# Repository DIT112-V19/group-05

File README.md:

# Route Design - The HAJKEN Car

<html> </html>

## What?

<i>“You draw, it drives!”</i>

An Android App in which the user can draw a (free-hand) route. The vehicle will drive according to the drawn route and, if requested, reverse and repeat it. Additionally, the vehicle can get its current GPS location and drive according to a track based on a route planned in google maps.

## Why?
The interface enables a simple way of controlling the vehicle without programming. Driving according to certain user-drawn route and reversing/repeating this route, can be used for:
* data collection 
* surveillance of area

There are many more applicable areas where there is use of a designed and predetermined route.

## How?
### Software:
#### for App
* Android Studio

#### for Arduino
* Arduino IDE
* Arduino libraries:
  * <a href="https://github.com/platisd/smartcar_shield">smartcar shield</a> by Dimitris Platis (*)
  * <a href="https://playground.arduino.cc/Code/NewPing/">NewPing</a> by Tim Eckel (*)
  * <a href="http://arduiniana.org/libraries/tinygpsplus/">TinyGPS++</a> by Mikal Hart
  
  (*) available via Arduino IDE  

### Hardware:
* Mobile Phone with Android OS and Bluetooth
* Arduino Mega
*  <a href="https://github.com/platisd/smartcar_shield/tree/master/extras/eagle/smartcar_shield">PCB Smartcar Shield</a>
* 4x DC motors
* Bluetooth module
* Sensors:
	* 2x UltraSonicSound Sensor (HC-SR04)
	* Odometer (speed encoders)
	* Gyroscope
	* GPS-module (Neo-6M)
* BETA: Hajken PCB with 3 LEDs and connections for sensors (see: pcb/hajken_cutouts_v2/)

## Setup and get Started

### Download repository
https://github.com/DIT112-V19/group-05/archieve/master.zip

### Car / Hardware
1. Follow the <a href="https://www.hackster.io/platisd/getting-started-with-the-smartcar-platform-1648ad">instructions</a> for the hardware setup of the smartcar with differential control (aka driving like a tank) 
2. Connect front UltraSonic Sensor to pin 51 (trigger) & pin 52 (echo) [or other equivalent free pins]
3. Connect right-side UltraSonic Sensor to pin 5 (trigger) & pin 6 (echo) [or other equivalent free pins] (or plugin into pins marked "Sensor right" on *Hajken PCB*)
4. Connect odometer to pin 3 (additional odometer: connect to pin 2) (or plugin into pins marked "Odometer right"/"Odometer left" on *Hajken PCB*)
5. Connect Bluetooth module to (hardware) serial 3 (pin 15(RX) & 14(TX) - connect RX to TX, TX to RX)
6. Connect GPS module to (hardware) serial 1 (pin 19(RX) & 18(TX) - connect RX to TX, TX to RX)

Hardware setup (with *Hajken PCB*):
<html>   </html>

### Arduino
1. Open hajkenCar.ino in Arduino IDE
2. Download the above-mentioned libraries (via Arduino IDE) and install TinyGPS++ manually (library folder must be called "TinyGPS++")
3. Adjust pin setup if necessary. 
4. Calibrate odometer(s) and gyroscope. Use Smartcar Shield sketches for calibration (Odometer: sensors->odometer->FindPulsesPerMeter / Gyroscope: sensors->odometer->GyroscopeCalibration). Update PULSES_PER_METER and GYRO_OFFSET values.
5. Optional: Test Sensors. Smartcar Shield library includes several sketches to test sensors' functionality.
6. Upload sketch to your Arduino Smartcar.

### Android Application

**1. Import Android Project**
* Open Android Studios
* Choose import project
* Select android inside of the cloned folder
* Follow setup instructions

**2. Create an API-key for Google Directions API** <br />
*This is required for the application to build.*<br />
* Go to the <a href="https://cloud.google.com/console/google/maps-apis/overview">Google Cloud Platform Console</a> .
* From the Project drop-down menu, select or create the project for which you want to add an API key.
* From the  Navigation menu, select APIs & Services > Credentials.
* On the Credentials page, click Create credentials > API key. <br />
The API key created dialog displays your newly created API key.
* Open the Android folder
* Create a copy of the file gradle.properties.no.git and name it gradle.properties
* Open gradle.properties
* Find line 15 where it says GoolgeAPIKey = "myKey"
* Insert your API-key where it says "myKey"

**3. Build and run the app in Android Studios** <br />
Tutorial for detailed instructions: https://developer.android.com/studio/run

**4. Give app permission to use location** <br />
Once the application is running, it needs permission to use the phones location.

| <html>   </html> |   <html>   </html> |   <html>   </html> |
 | --- | --- | --- |
| a). Open Settings. Go to Permissions | b). Go to Your Location | c). Enable permission for the app |

**5. The application is ready for using**

## Navigate through the interface

The basic navigation through the app can be seen in the following 3 pictures:

| Connect to car | Draw and drive | Map and drive |
  | --- | --- | --- |
| <html>   </html> |  <html>   </html> |   <html>   </html> |

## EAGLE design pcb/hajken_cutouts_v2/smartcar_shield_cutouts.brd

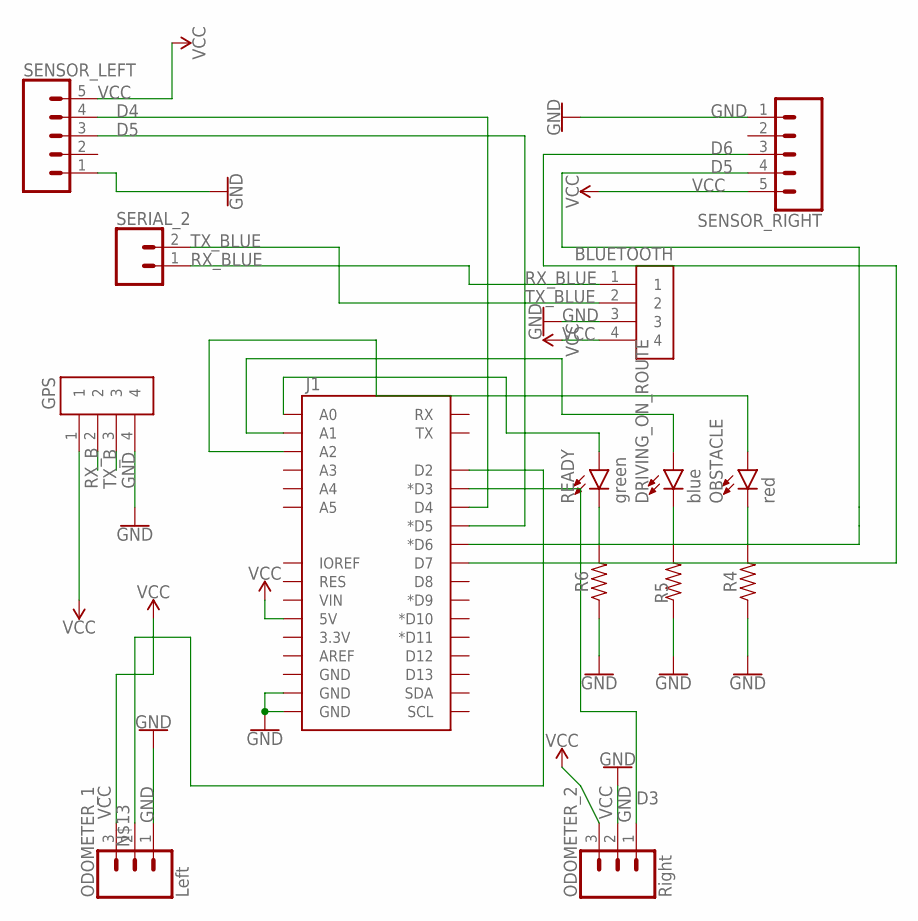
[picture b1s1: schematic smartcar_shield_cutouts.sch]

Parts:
BLUETOOTH: 1X4-BIG; 1X04-BIG
DRIVING_ON_ROUTE: blue; LED_5MM
GPS: 1X4-BIG; 1X04-BIG
J1: ARDUINO_R3_SHIELDUNO_R3_SHIELD_LOCK; UNO_R3_SHIELD_LOCK
OBSTACLE: red; LED_5MM
ODOMETER_1: Left; 1X03
ODOMETER_2: Right; 1X03
R4, R5, R6: AXIAL-0.3
READY: green; LED_5MM
SENSOR_LEFT: CONN_05; 1X05
SENSOR_RIGHT: CONN_05; 1X05
SERIAL_2: CONN_02; 1X02

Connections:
D3: J1.D3 (*D3), ODOMETER_2.1
D4: J1.D4, SENSOR_LEFT.4
D5: J1.D5 (*D5), J1.D6 (*D6), SENSOR_LEFT.3, SENSOR_RIGHT.4
D6: J1.D7, SENSOR_RIGHT.3
GND: BLUETOOTH.3, GPS.4, J1.GND@0 (GND), J1.GND@1 (GND), ODOMETER_1.1, ODOMETER_2.2, R4.P$1 (1), R5.P$1 (1), R6.P$1 (1), SENSOR_LEFT.1, SENSOR_RIGHT.1
unnamed: R6.P$2 (2), READY.K (C)
unnamed: DRIVING_ON_ROUTE.K (C), R5.P$2 (2)
unnamed: OBSTACLE.K (C), R4.P$2 (2)
unnamed: DRIVING_ON_ROUTE.A, J1.A1
unnamed: J1.D2, ODOMETER_1.2
unnamed: J1.A2, OBSTACLE.A
unnamed: J1.A0, READY.A
RX_B: GPS.2
RX_BLUE: BLUETOOTH.1, SERIAL_2.1
TX_B: GPS.3
TX_BLUE: BLUETOOTH.2, SERIAL_2.2
VCC: BLUETOOTH.4, GPS.1, J1.5V, ODOMETER_1.3, ODOMETER_2.3, SENSOR_LEFT.5, SENSOR_RIGHT.5

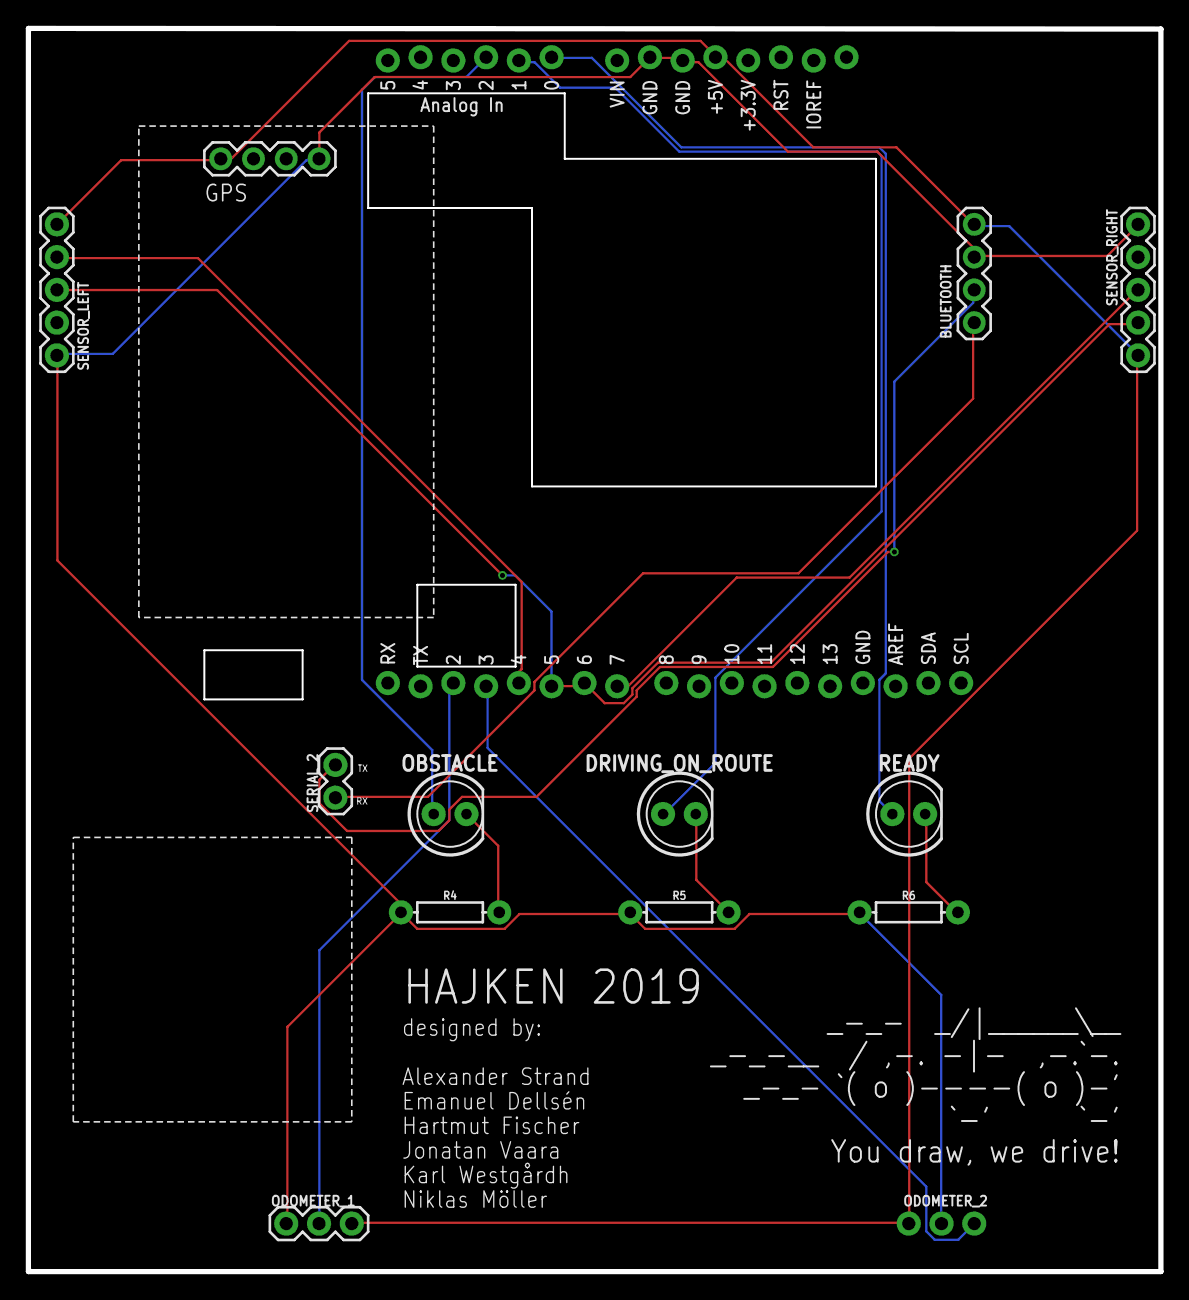
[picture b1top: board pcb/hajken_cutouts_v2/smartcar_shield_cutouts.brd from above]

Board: 2 copper layers, 87.8 x 96.4 mm, 14 parts (1 on the bottom side), 15 nets.

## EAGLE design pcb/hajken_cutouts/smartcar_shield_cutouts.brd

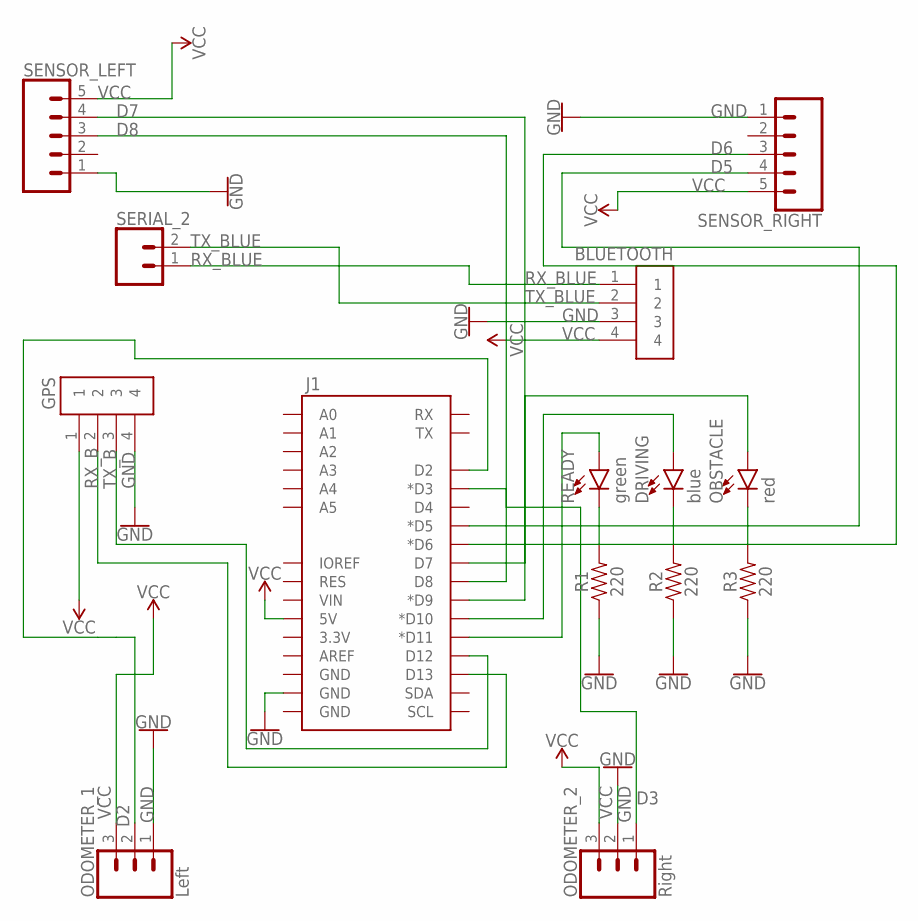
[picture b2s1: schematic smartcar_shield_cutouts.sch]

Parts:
BLUETOOTH: 1X4-BIG; 1X04-BIG
DRIVING: blue; LED_5MM
GPS: 1X4-BIG; 1X04-BIG
J1: ARDUINO_R3_SHIELDUNO_R3_SHIELD_LOCK; UNO_R3_SHIELD_LOCK
OBSTACLE: red; LED_5MM
ODOMETER_1: Left; 1X03
ODOMETER_2: Right; 1X03
R1, R2, R3: 220; 0603
READY: green; LED_5MM
SENSOR_LEFT: CONN_05; 1X05
SENSOR_RIGHT: CONN_05; 1X05
SERIAL_2: CONN_02; 1X02

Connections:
D2: J1.D2, ODOMETER_1.2
D3: J1.D3 (*D3), ODOMETER_2.1
D5: J1.D5 (*D5), SENSOR_RIGHT.4
D6: J1.D6 (*D6), SENSOR_RIGHT.3
D7: J1.D7, SENSOR_LEFT.4
D8: J1.D8, SENSOR_LEFT.3
GND: BLUETOOTH.3, GPS.4, J1.GND@1 (GND), ODOMETER_1.1, ODOMETER_2.2, R1.1, R2.1, R3.1, SENSOR_LEFT.1, SENSOR_RIGHT.1
unnamed: R1.2, READY.K (C)
unnamed 15: DRIVING.K (C), R2.2; also elsewhere on the board
unnamed: OBSTACLE.K (C), R3.2
unnamed: J1.D11 (*D11), READY.A
unnamed 19: DRIVING.A, J1.D10 (*D10); also elsewhere on the board
unnamed: J1.D9 (*D9), OBSTACLE.A
RX_B: GPS.2, J1.D13
RX_BLUE: BLUETOOTH.1, SERIAL_2.1
TX_B: GPS.3, J1.D12
TX_BLUE: BLUETOOTH.2, SERIAL_2.2
VCC: BLUETOOTH.4, GPS.1, J1.5V, ODOMETER_1.3, ODOMETER_2.3, SENSOR_LEFT.5, SENSOR_RIGHT.5

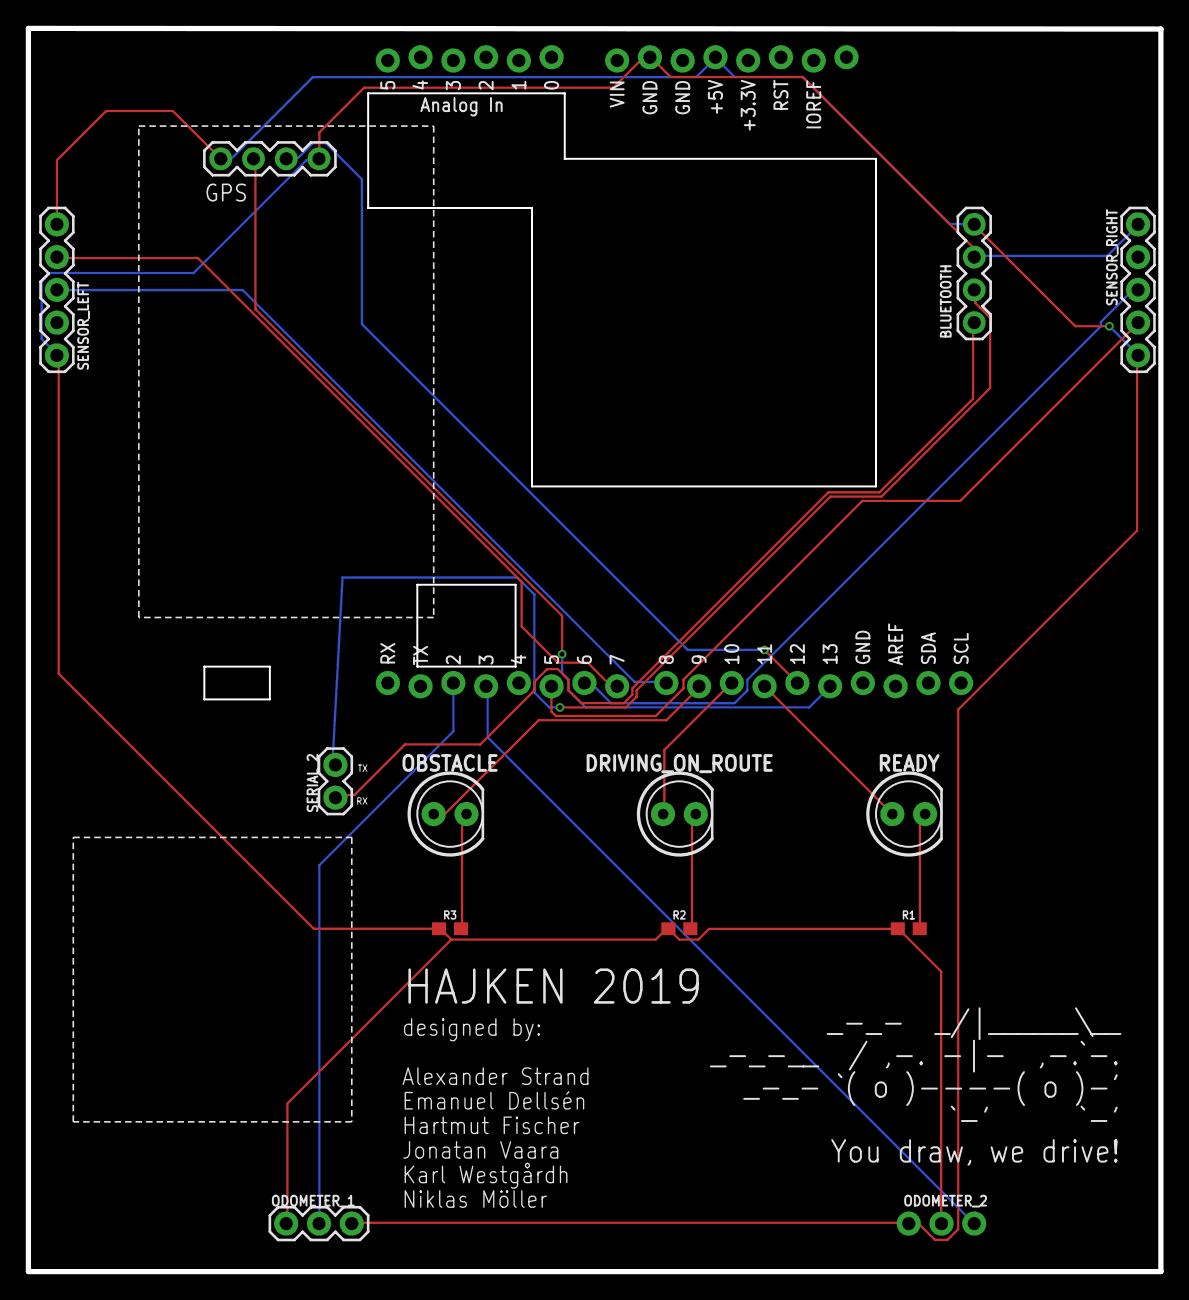
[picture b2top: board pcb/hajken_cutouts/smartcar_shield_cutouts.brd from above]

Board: 2 copper layers, 87.8 x 96.4 mm, 14 parts (1 on the bottom side), 18 nets.

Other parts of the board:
DRIVING_ON_ROUTE: blue; LED_5MM

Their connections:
unnamed 15: DRIVING_ON_ROUTE.K; also elsewhere on the board
unnamed 19: DRIVING_ON_ROUTE.A; also elsewhere on the board

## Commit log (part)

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2019-04-04 Subject:Olivers readme
2019-04-05 Create .gitignore
    Added a gitignore that covers; Intellij, Eclipse, Arduino, Android studios
2019-04-05 Subject: Add README file
    Describe why, how and what
2019-04-08 Added issue template
    Including labels, assignees and acceptance criteria
2019-04-10 Subject: Fixed basic layout
    Changed layout of the different fragments.
    Removed unnescessary green bar from top of the screen.
2019-04-10 Subject: Add basic forward/backward function
    Add forward driving function
    Add backward driving function
2019-04-10 Subject: Choice of route
    ImageButtons for choice of circle route or square route
    Included customDialog to interface
    Included customDialog via interface to mainActivity, used to display
    messages
    Included toast in mainactivity
2019-04-11 Subject: Integration of bluetooth
    Description:
    Starting the integration of bluetooth connectivity with the app.
    Updated class "scanFragment"
2019-04-11 Subject: Integrated bluetooth to code
    Description: Now scan for devices works, it produces a list of devices
    found and you can choose device and establish a bluetooth connection
    between your phone and that device.
2019-04-12 Subject:
2019-04-12 Subject: Fixed Layout
    Improved the layout of the app to look better.
    The buttons are now symmetrical.
    Added border to the device list.
    Added a colour for our standard background, however, standard background
    doesn't work yet.
2019-04-12 Subject: {SUBJECT_TITLE}
    {DESCRIPTION}
    Related Issue(s):
2019-04-14 Subject: Fixed "Stop Vehicle Button" states
    Changed the switch case in CollectionFragment so that the button changes
    states when user clicks on it.
    Now it represents the true state of the button (I Think)
    Fixes #21
2019-04-14 Subject: Add stop vehicle button
    - Stop vehicle button deactivated until vehicle has started
    - Stop vehicle button has its own related dialog
    - Collections and onbackPressed deactivated when vehicle has started
    Related issues:
    - Relates to #21
    - Relates to #20
2019-04-15 Subject: Minor changes regarding bluetooth connectivity
    Description: No big changes done
2019-04-15 Subject: Fix toasts and dialog changes
    Fix toast when onBackPressed
    Fix toast when cancelDialoge
    Change one line background color for pair_button
    Related Issues
    Relates to #21
2019-04-15 Subject: Add canvasDraw
    Add a way to draw on a canvas.
    Make sure it is only possible to make one line at a time.
    Give canvas a frame.
    Related Issues:
    Relates to #27
    Relates to #28
2019-04-16 Subject: Minor changes to bluetooth
    Description: Minor changes to bluetooth class
2019-04-17 Subject: Fix rotate function
    Why: To be able to make the car rotate
    What: Reading gyroscope value, to turn specified amount of angle
    Related Issue(s):
    Relates to #13 , #11
2019-04-17 Subject: Add function to stop vehicle
    Why: To be able to stop the vehicle, while moving
    What: Stop function that reads from serial, looks for 's' to stop
    Related Issue(s):
    Relates to #17 , #20
2019-04-29 Subject: Add vector calculation
    Coordinates saved are now relevant to the direction and rotation of the
    vehicle
2019-04-29 Subject: Correct coordinate conversion
    - Corrected coordinate conversion
    - Able to send instructions to vehicle via bluetooth
2019-04-30 Subject: Clean up and comments
    Why: Making code look good and understandable
    What: Clean up irrelevant code and add some comments
    Authors:
    Related Issue(s): Relates to #31
2019-05-02 Subject: Add RDP-algorithm
    Description: Add RDP-algorithm to simplify polyline drawn from
    application
2019-05-03 Subject: Reverse commands and rounds to drive
    Why: Being able to going back and forth on a predetermined route
    What: Reading command inputs backwards and executing them. Executing
    commands for a given amount of time
    Authors: Co-authored-by: HarFis <gusfisha@student.gu.se>
    Related Issue(s): Fixes #32 , Relates to #39
2019-05-03 Subject: Merge commented and reverse function
2019-05-03 Subject: Fixed instructions rotation
    Description:
    - Fixed coordinateConverter rotation for user interface
    - Changed instructions syntax for reverse/loop
2019-05-03 Subject: Added function to call vechile for GPS-data
    Description: Inserted BluetoothConnection in OnAttach
    Relates #37 & #41
2019-05-03 Subject: Notify when no connection in collection
    Create a toast to display to the user which says "Not Connected to a
    device". This is only for the Collection Fragment.
    This will help the user-experience.
2019-05-06 Subject: Button funcionality and show device
    Add Button functionality in the drawFragment.
    Connected device is now displayed in some of the fragments.
2019-05-06 travis setup
2019-05-06 Subject: Colour changes
    Changed colours for the buttons and the Fragments' background
2019-05-06 Update .travis.yml
    Removed duplicate code which disabled the CI
2019-05-06 Subject: Change position of google maps-fragment entry
    Description:
    - Change position of google maps-fragment entry to gatewayFragment
2019-05-06 Subject: RecyclerView
    Add basic recyclerView functionality.
    It is scorlled verically instead of horizontally for now.
    Also, the pictures have no onClickListeners yet.
    Relates to #52
2019-05-06 Subject: Deleted unused arduino file
    Description: Deleted unused arduino file that is unused and causes error
    upon running travis.yml script
2019-05-06 Update ExampleInstrumentedTest.java
    Change in the androidTest folder because it gave an error in the travis CI test
2019-05-06 Update .travis.yml
    Update to a newer tinyGPSPlus library in the travis.yml
2019-05-07 Update .travis.yml
    Add a way to deal with the library based on a suggestion from @platisd
2019-05-08 Update hajkenCar.ino
    Remove merge conflicts
2019-05-08 Subject: Refractoring
    Removal of unused classes
2019-05-08 Subject: Heading correction and stoping method
    Why: Veichle should drive in a straight line, vechile should be able to
    stop
    What: Method that checks veichle current heading and corrects the
    heading with differnet motor speed, update speed to three different
    choices
    Authors: Co-authored-by: HarFis <gusfisha@student.gu.se>
2019-05-08 Subject: Add working recyclerView
    Add functionallity when pressing images in recyclerView.
    Also, add nested ArrayList with coordinates in OurData.
    Fixes #52
2019-05-08 Subject: Add radiogroup/buttons
    Description:
    - Add radiogroup to drawFragment and collectionFragment
    - Add radiobutton to drawFragment and collectionFragment to change speed
    of vehicle instructions
2019-05-08 Subject: add button states
    Description:
    - Add button correct states
    - Add button layout
2019-05-10 Subject: Fix buttons
    Add buttons to mapFragment.
    Change name of buttons on draw and collection.
2019-05-10 Subject: Add PCB cutout files
2019-05-10 Subject: Add dialog fragment, button states in scan fragment, listener
    Description: Add a dialog fragment in draw fragment from which you can start and stop the car. Altered button states in scan fragment so they adapt with bluetooth status with the use of interface and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
    Fixes #42
    Relates to #51
2019-05-11 Subject: Update PCB board - ready for production
2019-05-12 Subject: Add listener to collection fragment
    Description: In progress to fully add listener to collection fragment to
    control button states and clarify connection status between devices
2019-05-12 Subject: Add bitmaps to recycler view
    Description: Add bitmaps to recycler view, class to bind each bitmap
    together with its respective coordinates
2019-05-13 Subject: Change small fix
    relate(s): #69
2019-05-13 Subject: Set API-key in Travis as enviroment variable
    Description: Set API-key as enviroment variable in the Travis Settings.
2019-05-14 Subject: Add bluetooth not enabled check
    Description:
    - Add bluetooth not enabled / non-existing check
2019-05-14 Subject: Add startPoint and display of actual route
    Description:
    - Add startPoint to canvas onDraw
    - Add display of actual route on canvas
    - Change color of drawn route to differ between drawn route and actual
    route
2019-05-15 Subject: Add dialog window to collection fragment
    Description: Add dialog window to collection fragment so that the user can alter speed of saved routes and number of repetitions then starts car after pressing start in the dialog window
2019-05-15 Subject: Add GPS function
    Why: Get position from GPS modul on start of map modus
    What: Read GPS signal on start of map modus, wait until GPS fix, leave on signal from app
    relates #70
2019-05-15 Subject: Removed one line from String.xml
2019-05-16 Subject: Start refactor bluetooth
    Description: Started refactoring of bluetooth to shift and place responsabilities correctly and decouple
2019-05-16 Subject: Update GPS function
    Why: GPSFunction did not work before
    What: Returns one coordinate of vehicle currents position
    Authors:
    Related Issue(s): #70
2019-05-16 Subject: Add listener for google maps fragment
    Description: Add listener for google maps fragment so that the button
    states changes accordingly to listener status
    Relates to #94 #89
2019-05-17 Subject: Update bypass function & add prints to app
    Why: Problem with bypass function, commands to communcate with app
    What: change while loop conditions, add command after finishing command row, back from bypass and obstacle detection
    relates #97 & #69
2019-05-20 Subject: Add GPSConnector and GPSTracker
    Description: Moving responsibility to connect to GPS from
    GoogleMapsFragment to GPSConnector. Implementing GPSTracker to retrieve
    GPS-location from users phone.
2019-05-22 Subject: Correct turning error
    Why: Vehicle sometimes overturned or underturned
    What: Fix by adding recursive call of rotate function, if turn was
    over or under target
    Authors:
    Related Issue(s):
    Fixes #96
2019-05-22 Subject: Add Functioning Saving
    Add the option to save drawings, to later use them.
    Did this by saving bitmap as a PNG, and saving an object as a Json file.
    Relates to #98
2019-05-24 Subject: Add Highlight on selected item
    This adds the funtion that highlights selected item in the collection
    fragment.
    Fixes #98
2019-05-24 Subject: Add GPS-communication between car & phone
    Description: Phone is now getting a GPS-position from the GPS-Sensor on
    the car. If there is no connection, the phone takes its GPS-position
    instead.
    [3~
2019-05-24 Subject: Add button text changes
    Description:
    - Button text in drawFragment changes when vehicle is running
2019-05-25 Subject: Fix bug
    Description:
    - removed hardcoded location in gpsTracker
2019-05-26 Subject: Refactoring
    Description:
    - Refactoring and replacement of code in all fragments and related xml
    §
2019-05-27 Subject: Finish obstacle bypass, update direction correction
    Why: more buffer between object needed, more power to correction needed
    What: direction correction increased correction speed, small adjustment in passing object
    Fixes #108
    Fixes #69
    Relate #97
2019-05-27 Subject: Adding images as cards with HTML
2019-05-27 Subject: Modified HTML
2019-05-27 Subject: Refactor arduino code
    Why: To have readable and understandable code
    What: Removing unnecessary code, old function, adding comments
    Authors:
    Related Issue(s):
    Relates to #106
2019-05-27 Subject: Add instructions to set up API key
2019-05-27 Subject: Add comment
    Why: Readable code
    What:
    Authors:
    Related Issue(s): #106
2019-05-27 Subject: Add interface and refactor
    Description: Add interface for VehicleListner and ConnectionListner
2019-05-28 Subject: Refactor adruino code
    Why/what: improve readability and structure
    Relates: #106
2019-05-29 Subject: Update readme file
2019-05-29 Subject: Update
2019-05-29 Subject: update readme
2019-05-29 SUbject: change readme
2019-05-31 Subject: updated readme

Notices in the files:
parts and their libraries:
SparkFun-Boards: Licensing: Creative Commons ShareAlike 4.0 International - https://creativecommons.org/licenses/by-sa/4.0
